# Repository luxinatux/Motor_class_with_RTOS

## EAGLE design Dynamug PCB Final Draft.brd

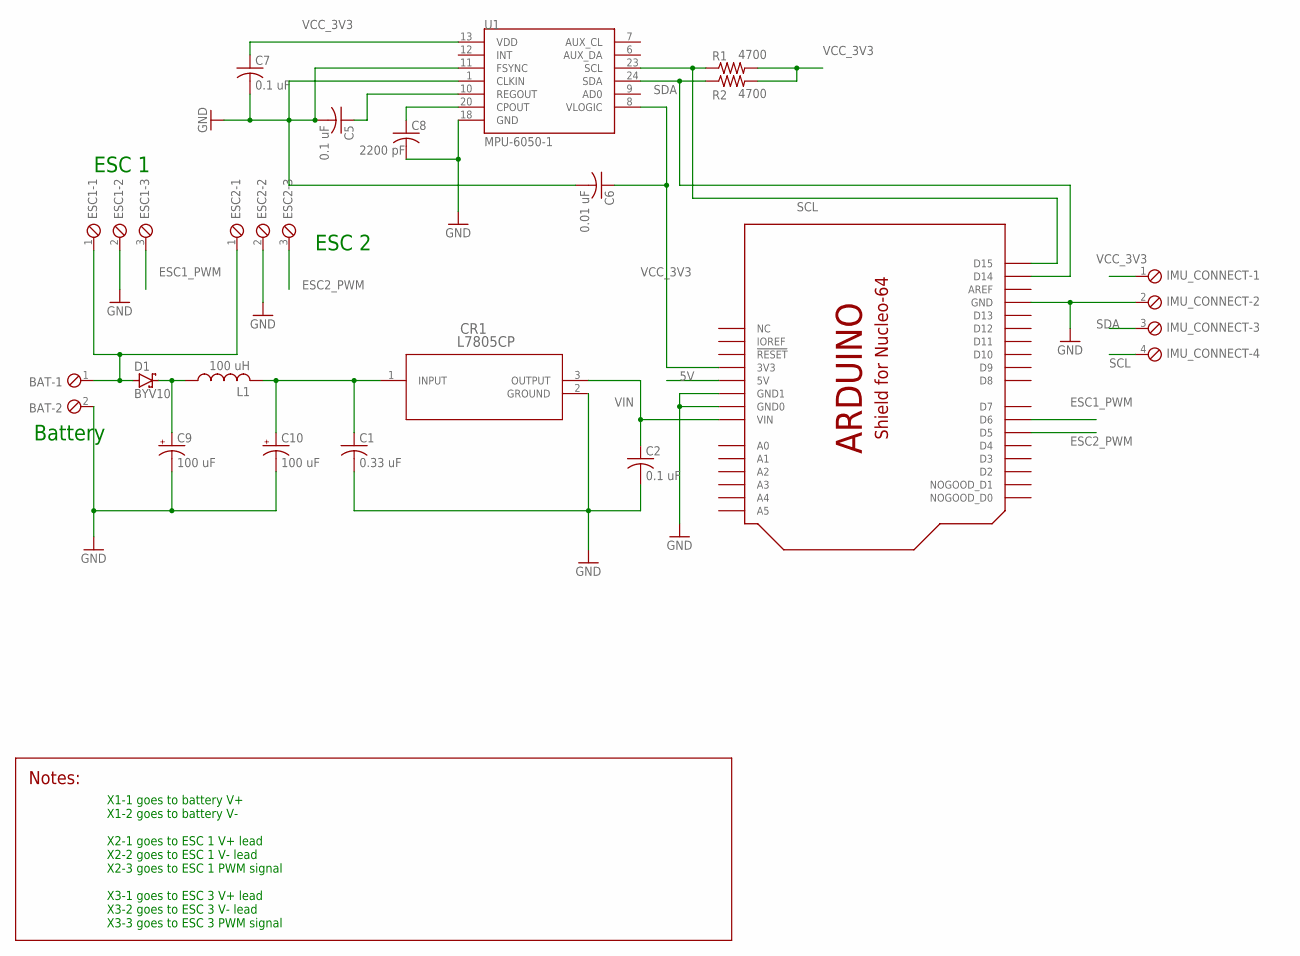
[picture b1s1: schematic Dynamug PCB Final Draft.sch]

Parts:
BAT: SCREWTERM_2P_381; 2POL381
C1: 0.33 uF; C0805
C2, C5, C7: 0.1 uF; C0805
C6: 0.01 uF; C0805
C8: 2200 pF; C0805
C9, C10: 100 uF; E2,5-6
CR1: L7805CP; TO-220FP_STM
D1: BYV10; DO41-10
ESC1, ESC2: SCREWTERM_3P_381; 3POL381
IMU_CONNECT: SCREWTERM_4P_381; 4POL381
L1: 100 uH; LAL03
R1, R2: 4700; R2010
U1: MPU-6050-1; QFN-24-4MM2
U$1: SHIELD_FOR_NUCLE0_64_SHORT; SHIELD_FOR_NUCLEO_64_SHORT

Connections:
5V: U$1.5V
ESC1_PWM: ESC1.3, U$1.D6
ESC2_PWM: ESC2.3, U$1.D5
GND: BAT.2, C1.2, C2.2, C5.2, C6.2, C7.2, C8.2, C9.-, C10.-, CR1.2 (GROUND), ESC1.2, ESC2.2, IMU_CONNECT.2, U1.1 (CLKIN), U1.11 (FSYNC), U1.18 (GND), U$1.GND, U$1.GND1 (GND0), U$1.GND2 (GND1)
unnamed: C1.1, C10.+, CR1.1 (INPUT), L1.2
unnamed: C9.+, D1.C, L1.1
unnamed: C5.1, U1.10 (REGOUT)
unnamed: C8.1, U1.20 (CPOUT)
SCL: IMU_CONNECT.4, R1.1, U1.23 (SCL), U$1.D15
SDA: IMU_CONNECT.3, R2.1, U1.24 (SDA), U$1.D14
VCC_3V3: C6.1, C7.1, IMU_CONNECT.1, R1.2, R2.2, U1.8 (VLOGIC), U1.13 (VDD), U$1.3V (3V3)
VIN: C2.1, CR1.3 (OUTPUT), U$1.VIN
V_BAT: BAT.1, D1.A, ESC1.1, ESC2.1

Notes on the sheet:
ESC 1
Battery
X1-1 goes to battery V+ X1-2 goes to battery V- X2-1 goes to ESC 1 V+ lead X2-2 goes to ESC 1 V- lead X2-3 goes to ESC 1 PWM signal X3-1 goes to ESC 3 V+ lead X3-2 goes to ESC 3 V- lead X3-3 goes to ESC 3 PWM signal
ESC 2

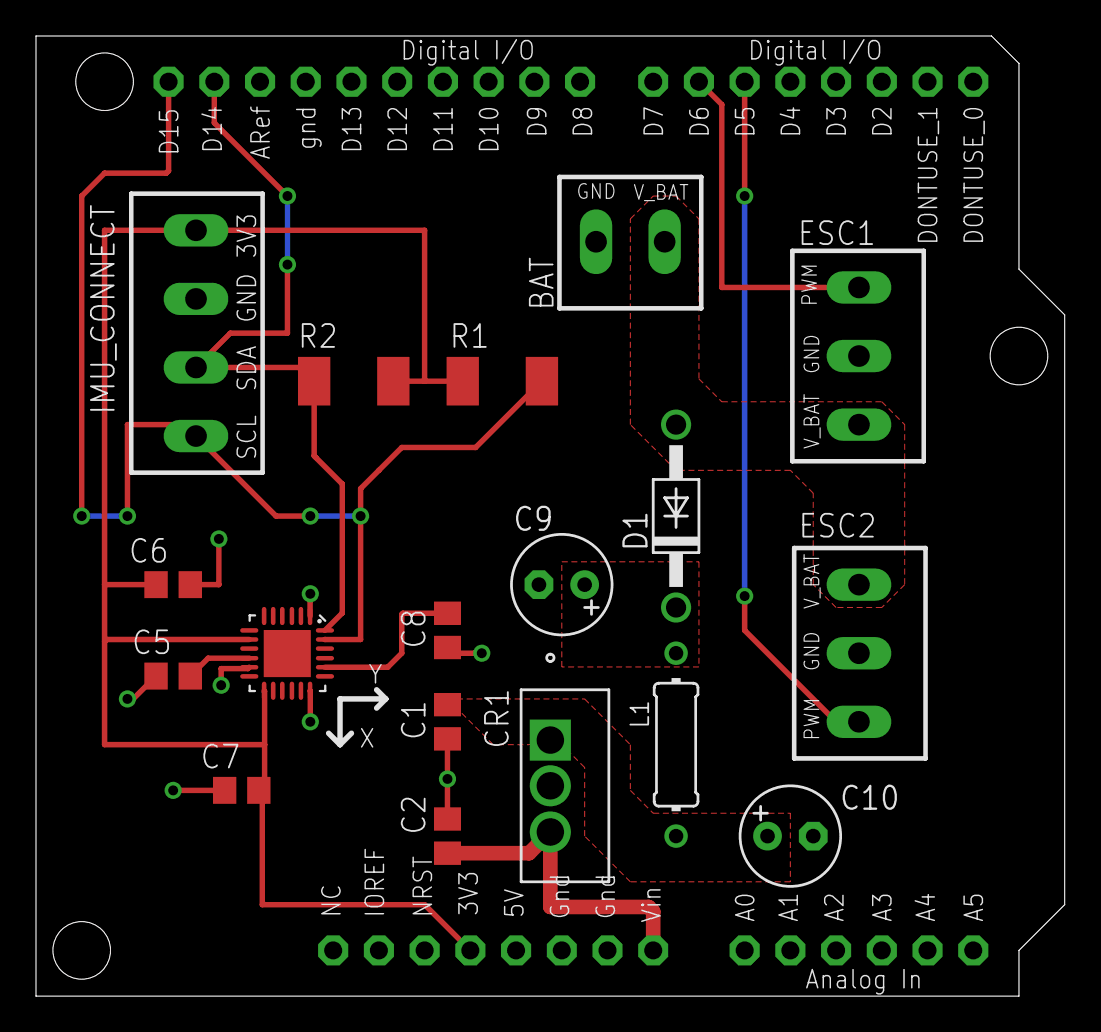
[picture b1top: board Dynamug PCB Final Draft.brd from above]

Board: 2 copper layers, 57.1 x 53.3 mm, 19 parts (0 on the bottom side), 12 nets.

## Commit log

2021-12-02 initial push
2021-12-02 adding MPU6050 header files
2021-12-02 change
2021-12-07 renamed
2021-12-07 changed name of taske
2021-12-07 minor changes
2021-12-07 minor change
2021-12-07 adding motor class
2021-12-07 finally
2021-12-07 edits to the controller task
2021-12-08 modified
2021-12-08 Removal of unused variables
2021-12-08 begining of doxygen style comments
2021-12-08 more doxygen
2021-12-08 final doxygen comments
2021-12-08 doxygen
2021-12-08 adding reference material
2021-12-08 adding Mug print stl files
2021-12-08 Eagle files
2021-12-08 doxygen and updates
2021-12-08 motor 2
2021-12-08 adding share for switching controller state
2021-12-08 overall updates to this task
2021-12-08 overall updates to this doxy
2021-12-08 final doxy comments

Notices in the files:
parts and their libraries:
COPYRIGHT: Copyright (C) 2021 Ultra Librarian. All rights reserved.
